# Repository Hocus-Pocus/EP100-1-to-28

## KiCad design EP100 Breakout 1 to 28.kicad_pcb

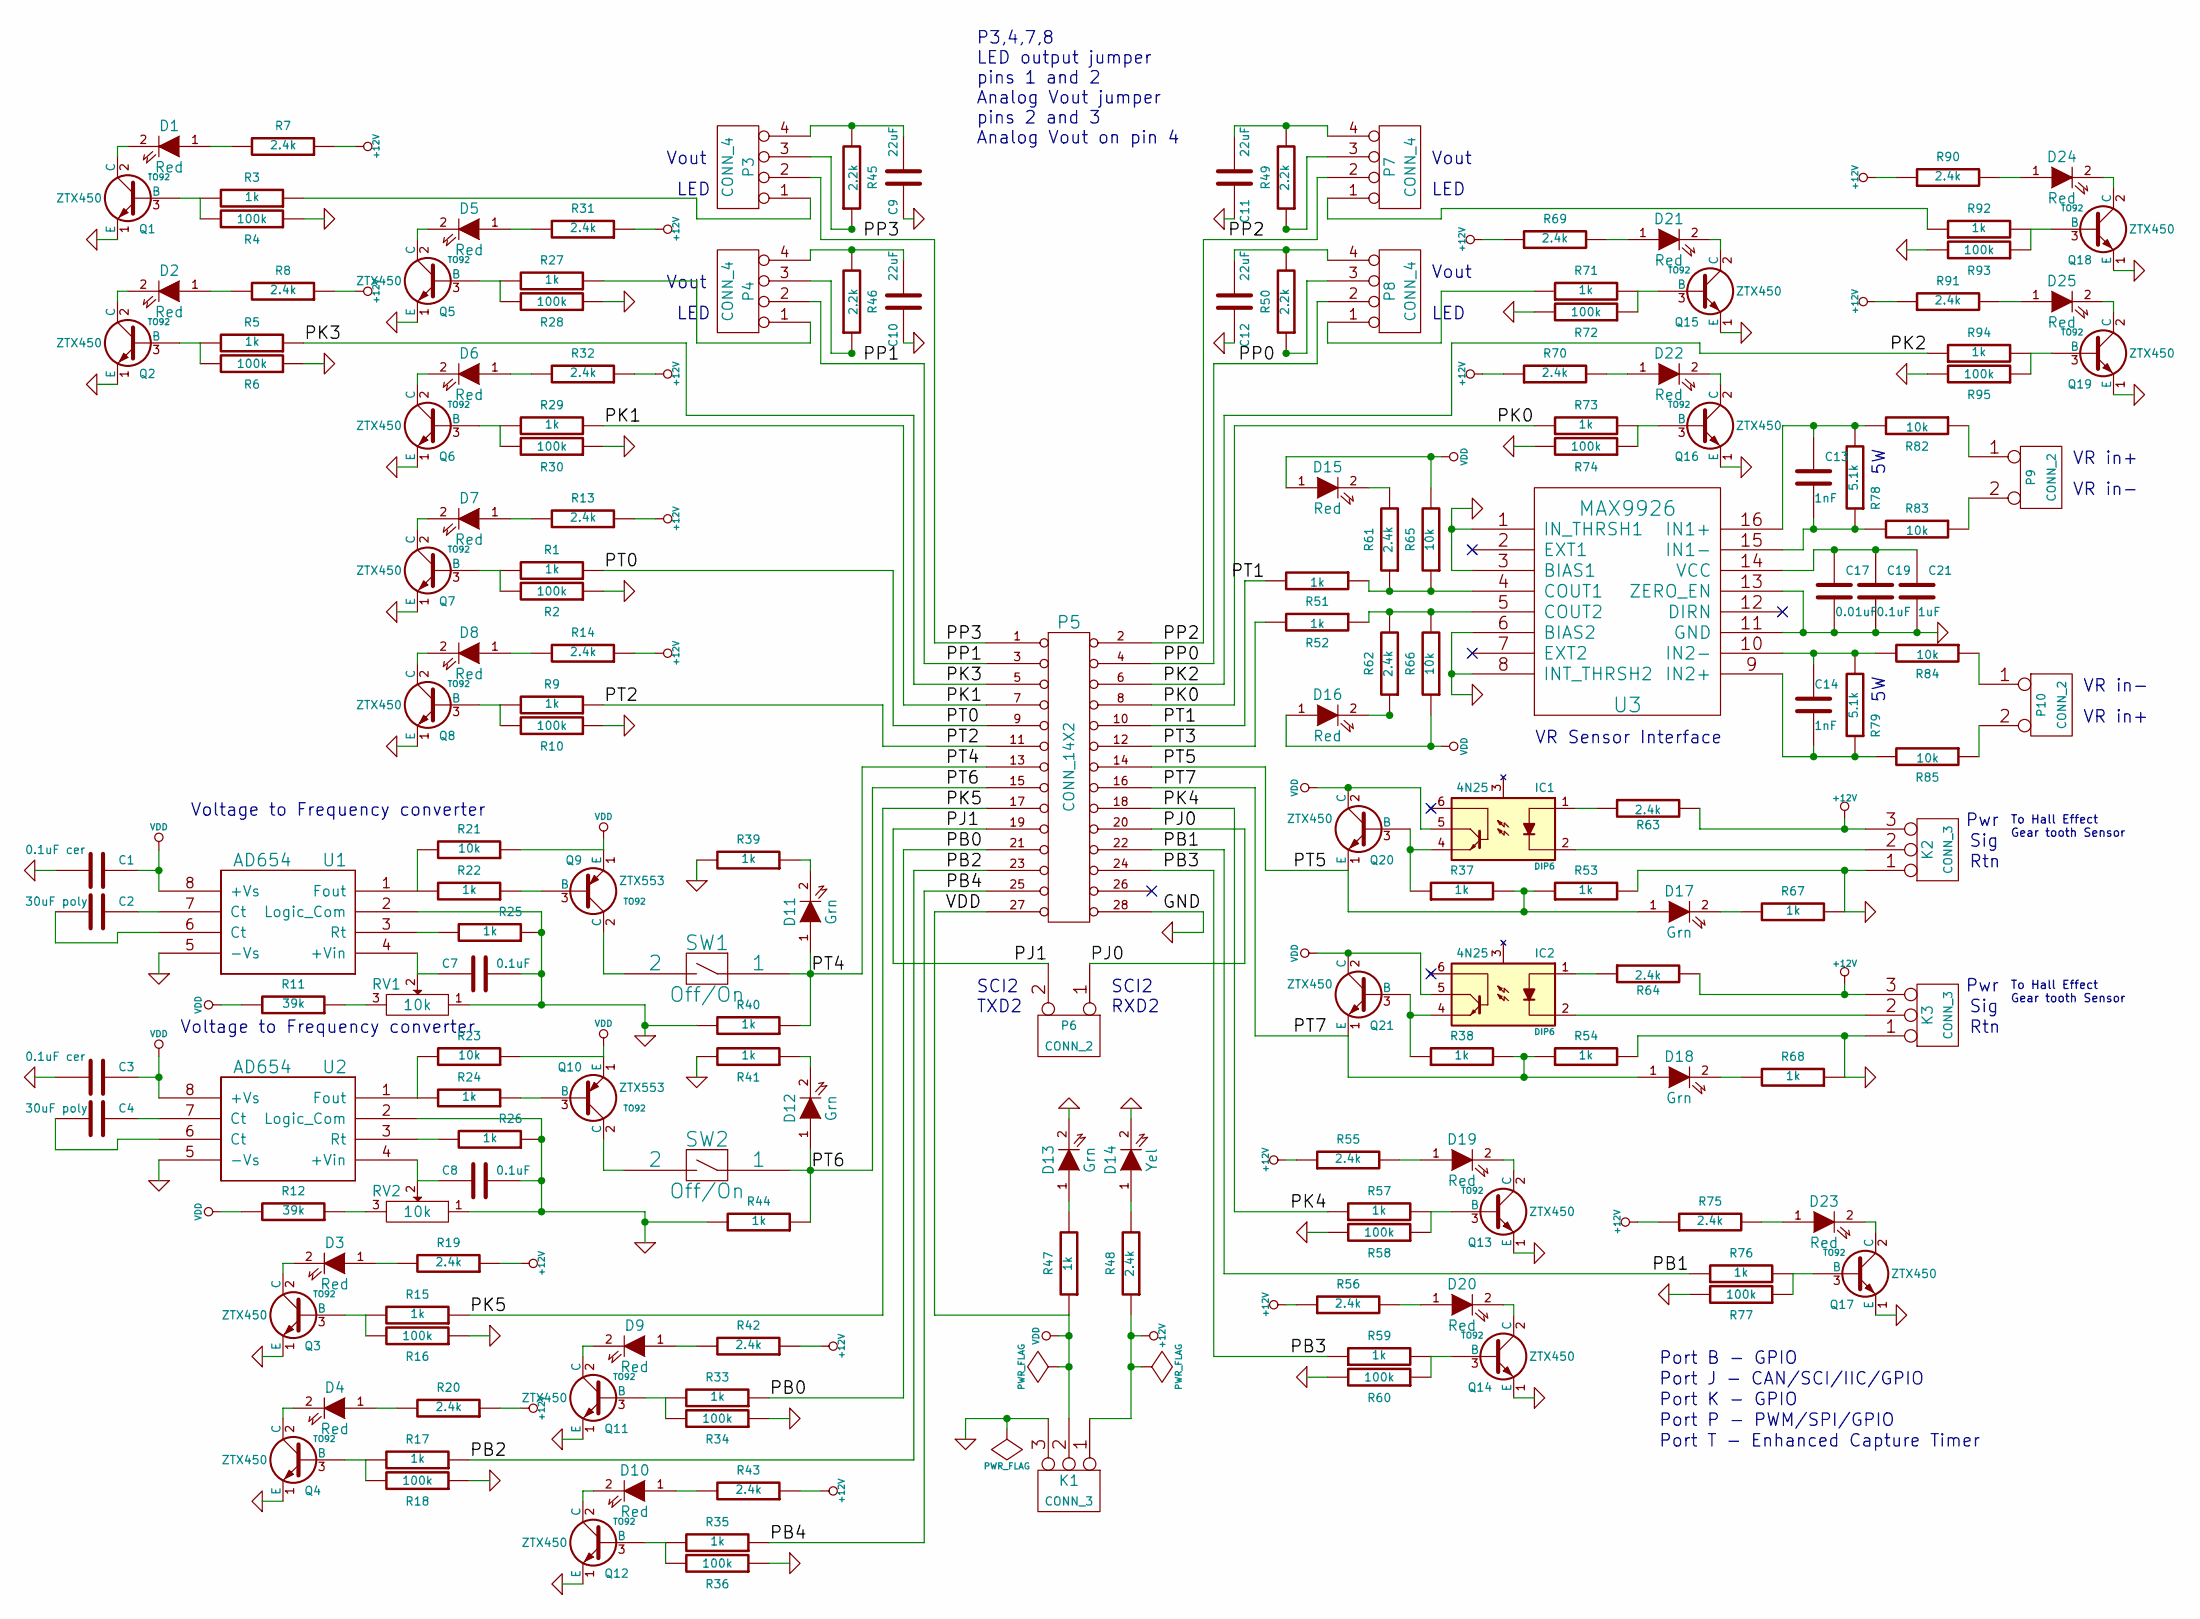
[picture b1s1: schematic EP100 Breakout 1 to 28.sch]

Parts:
C1, C3: 0.1uF cer
C2, C4: 30uF poly
C7, C8, C19: 0.1uF
C9, C10, C11, C12: 22uF
C13, C14: 1nF
C17: 0.01uF
C21: 1uF
D1, D2, D3, D4, D5, D6, D7, D8, D9, D10, D15, D16, D19, D20, D21, D22, D23, D24, D25: Red
D11, D12, D13, D17, D18: Grn
D14: Yel
IC1, IC2: 4N25; DIP6
K1, K2, K3: CONN_3
P3, P4, P7, P8: CONN_4
P5: CONN_14X2
P6, P9, P10: CONN_2
Q1, Q2, Q3, Q4, Q5, Q6, Q7, Q8, Q11, Q12, Q13, Q14, Q15, Q16, Q17, Q18, Q19: ZTX450; TO92
Q9, Q10: ZTX553; TO92
Q20, Q21: ZTX450; TO126
R1, R3, R5, R9, R15, R17, R22, R24, R25, R26, R27, R29, R33, R35, R37, R38, R39, R40, R41, R44, R47, R51, R52, R53, R54, R57, R59, R67, R68, R71, R73, R76, R92, R94: 1k
R2, R4, R6, R10, R16, R18, R28, R30, R34, R36, R58, R60, R72, R74, R77, R93, R95: 100k
R7, R8, R13, R14, R19, R20, R31, R32, R42, R43, R48, R55, R56, R61, R62, R63, R64, R69, R70, R75, R90, R91: 2.4k
R11, R12: 39k
R21, R23, R65, R66, R82, R83, R84, R85: 10k
R45, R46, R49, R50: 2.2k
R78, R79: 5.1k
RV1, RV2: 10k
SW1, SW2: Off/On
U1, U2: AD654
U3: MAX9926

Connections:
+12V: K1.1, K2.3, K3.3, R7.1, R8.1, R13.1, R14.1, R19.1, R20.1, R31.1, R32.1, R42.1, R43.1, R48.1, R55.1, R56.1, R63.2, R64.2, R69.1, R70.1, R75.1, R90.1, R91.1
/PB0: P5.21, R33.1
/PB1: P5.22, R76.1
/PB2: P5.23, R17.1
/PB3: P5.24 (P20), R59.1
/PB4: P5.25, R35.1
/PJ0: P5.20, P6.1
/PJ1: P5.19, P6.2 (PM)
/PK0: P5.8, R73.1
/PK1: P5.7, R29.1
/PK2: P5.6, R94.1
/PK3: P5.5, R5.1
/PK4: P5.18, R57.1
/PK5: P5.17, R15.1
/PP0: P5.4, P8.2
/PP1: P4.2, P5.3
/PP2: P5.2, P7.2
/PP3: P3.2, P5.1
/PT0: P5.9, R1.1
/PT1: P5.10, R51.2
/PT2: P5.11, R9.1
/PT3: P5.12, R52.2
/PT4: D11.1 (A), P5.13, R40.1, SW1.1
/PT5: D17.1 (A), P5.14, Q20.1 (E), R37.2, R53.1
/PT6: D12.1 (A), P5.15, R44.1, SW2.1
/PT7: D18.1 (A), P5.16, Q21.1 (E), R38.2, R54.1
GND: C1.2, C3.2, C7.2, C8.2, C9.1, C10.1, C11.1, C12.1, C17.2, C19.2, C21.2, D13.2 (K), D14.2 (K), K1.3, K2.1, K3.1, P5.28, Q1.1 (E), Q2.1 (E), Q3.1 (E), Q4.1 (E), Q5.1 (E), Q6.1 (E), Q7.1 (E), Q8.1 (E), Q11.1 (E), Q12.1 (E), Q13.1 (E), Q14.1 (E), Q15.1 (E), Q16.1 (E), Q17.1 (E), Q18.1 (E), Q19.1 (E), R2.1, R4.1, R6.1, R10.1, R16.1, R18.1, R25.1, R26.1, R28.1, R30.1, R34.1, R36.1, R39.2, R40.2, R41.2, R44.2, R53.2, R54.2, R58.2, R60.2, R67.1, R68.1, R72.2, R74.2, R77.2, R93.2, R95.2, RV1.1, RV2.1, U1.2 (Logic_Com), U1.5 (-Vs), U2.2 (Logic_Com), U2.5 (-Vs), U3.1 (IN_THRSH1), U3.3 (BIAS1), U3.6 (BIAS2), U3.8 (INT_THRSH2), U3.11 (GND), U3.13 (ZERO_EN)
unnamed: C2.2, U1.6 (Ct)
unnamed: C2.1, U1.7 (Ct)
unnamed: Q14.3 (B), R59.2, R60.1
unnamed: D20.2 (K), Q14.2 (C)
unnamed: D20.1 (A), R56.2
unnamed: R25.2, U1.3 (Rt)
unnamed: R21.2, R22.2, U1.1 (Fout)
unnamed: R11.1, RV1.3
unnamed: D25.2 (K), Q19.2 (C)
unnamed: Q15.3 (B), R71.2, R72.1
unnamed: D21.2 (K), Q15.2 (C)
unnamed: D21.1 (A), R69.2
unnamed: Q19.3 (B), R94.2, R95.1
unnamed: D25.1 (A), R91.2
unnamed: Q16.3 (B), R73.2, R74.1
unnamed: D22.2 (K), Q16.2 (C)
unnamed: D22.1 (A), R70.2
unnamed: D15.2 (K), R61.2
unnamed: D16.2 (K), R62.1
unnamed: D24.1 (A), R90.2
unnamed: D14.1 (A), R48.2
unnamed: D13.1 (A), R47.2
unnamed: Q4.3 (B), R17.2, R18.2
unnamed: Q5.3 (B), R27.2, R28.2
unnamed: D5.2 (K), Q5.2 (C)
unnamed: D5.1 (A), R31.2
unnamed: D4.2 (K), Q4.2 (C)
unnamed: P10.1, R84.1
unnamed: P10.2 (PM), R85.1
unnamed: P9.2 (PM), R83.1
unnamed: P9.1, R82.1
unnamed: D4.1 (A), R20.2
unnamed: Q12.3 (B), R35.2, R36.2
unnamed: D10.2 (K), Q12.2 (C)
unnamed: D10.1 (A), R43.2
unnamed: Q3.3 (B), R15.2, R16.2
unnamed: D3.2 (K), Q3.2 (C)
unnamed: D3.1 (A), R19.2
unnamed: C4.2, U2.6 (Ct)
unnamed: C4.1, U2.7 (Ct)
unnamed: D8.2 (K), Q8.2 (C)
unnamed: Q8.3 (B), R9.2, R10.2
unnamed: D9.2 (K), Q11.2 (C)
unnamed: D9.1 (A), R42.2
unnamed: R23.2, R24.2, U2.1 (Fout)
unnamed: R26.2, U2.3 (Rt)
unnamed: R12.1, RV2.3
unnamed: D18.2 (K), R68.2
unnamed: D8.1 (A), R14.2
unnamed: D7.2 (K), Q7.2 (C)
unnamed: Q11.3 (B), R33.2, R34.2
unnamed: Q7.3 (B), R1.2, R2.2
unnamed: D7.1 (A), R13.2
unnamed: Q13.3 (B), R57.2, R58.1
unnamed: D19.2 (K), Q13.2 (C)
unnamed: D19.1 (A), R55.2
unnamed: D23.2 (K), Q17.2 (C)
unnamed: Q17.3 (B), R76.2, R77.1
unnamed: D1.1 (A), R7.2
unnamed: D23.1 (A), R75.2
unnamed: IC2.4, Q21.3 (B), R38.1
unnamed: IC1.1, R63.1
unnamed: IC1.4, Q20.3 (B), R37.1
unnamed: IC2.1, R64.1
unnamed: P3.3, R45.1
unnamed: C8.1, RV2.2, U2.4 (+Vin)
unnamed: C7.1, RV1.2, U1.4 (+Vin)
unnamed: P8.1, R71.1
unnamed: P7.1, R92.1
unnamed: D17.2 (K), R67.2
unnamed: IC1.2, K2.2 (PM)
unnamed: Q10.2 (C), SW2.2
unnamed: IC2.2, K3.2 (PM)
unnamed: Q18.3 (B), R92.2, R93.1
unnamed: D24.2 (K), Q18.2 (C)
unnamed: Q9.2 (C), SW1.2
unnamed: Q1.3 (B), R3.2, R4.2
unnamed: Q6.3 (B), R29.2, R30.2
unnamed: Q2.3 (B), R5.2, R6.2
unnamed: D2.2 (K), Q2.2 (C)
unnamed: D2.1 (A), R8.2
unnamed: D6.2 (K), Q6.2 (C)
unnamed: D6.1 (A), R32.2
unnamed: D1.2 (K), Q1.2 (C)
unnamed: D11.2 (K), R39.1
unnamed: Q9.3 (B), R22.1
unnamed: D12.2 (K), R41.1
unnamed: Q10.3 (B), R24.1
unnamed: P7.3, R49.1
unnamed: P4.1, R27.1
unnamed: P3.1, R3.1
unnamed: P8.3, R50.1
unnamed: P4.3, R46.1
unnamed: C14.2, R79.1, R85.2, U3.9 (IN2+)
unnamed: C14.1, R79.2, R84.2, U3.10 (IN2-)
unnamed: C13.1, R78.2, R82.2, U3.16 (IN1+)
unnamed: C13.2, R78.1, R83.2, U3.15 (IN1-)
unnamed: R52.1, R62.2, R66.2, U3.5 (COUT2)
unnamed: R51.1, R61.1, R65.1, U3.4 (COUT1)
unnamed: C17.1, C19.1, C21.1, U3.14 (VCC)
unnamed: C11.2, P7.4, R49.2
unnamed: C10.2, P4.4, R46.2
unnamed: C12.2, P8.4, R50.2
unnamed: C9.2, P3.4, R45.2
VDD: C1.1, C3.1, D15.1 (A), D16.1 (A), IC1.5, IC2.5, K1.2 (PM), P5.27, Q9.1 (E), Q10.1 (E), Q20.2 (C), Q21.2 (C), R11.2, R12.2, R21.1, R23.1, R47.1, R65.2, R66.1, U1.8 (+Vs), U2.8 (+Vs)

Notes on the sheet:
VR in+
VR in-
SCI2 TXD2
SCI2 RXD2
Vout
LED
Port B - GPIO
Port J - CAN/SCI/IIC/GPIO
Port K - GPIO
Port P - PWM/SPI/GPIO
Port T - Enhanced Capture Timer
Voltage to Frequency converter
VR Sensor Interface
P3,4,7,8 LED output jumper pins 1 and 2 Analog Vout jumper pins 2 and 3 Analog Vout on pin 4
Pwr
Sig
Rtn
To Hall Effect Gear tooth Sensor

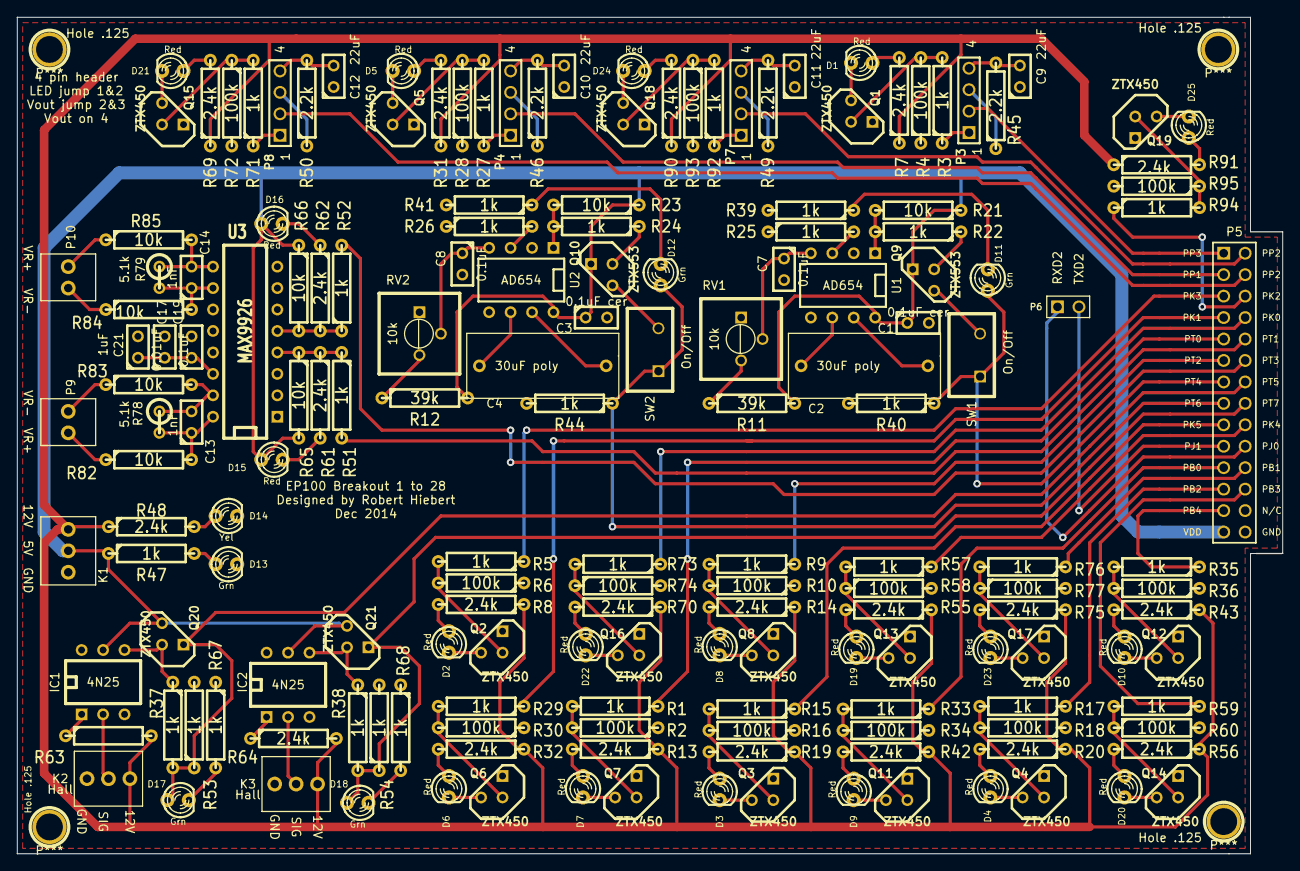
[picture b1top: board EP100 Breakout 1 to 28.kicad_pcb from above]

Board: 2 copper layers, 149.9 x 99.1 mm, 174 parts (0 on the bottom side), 132 nets.

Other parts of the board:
Hole .125, Hole .125#2, Hole .125#3, Hole .125#4: P***; Hole.125
